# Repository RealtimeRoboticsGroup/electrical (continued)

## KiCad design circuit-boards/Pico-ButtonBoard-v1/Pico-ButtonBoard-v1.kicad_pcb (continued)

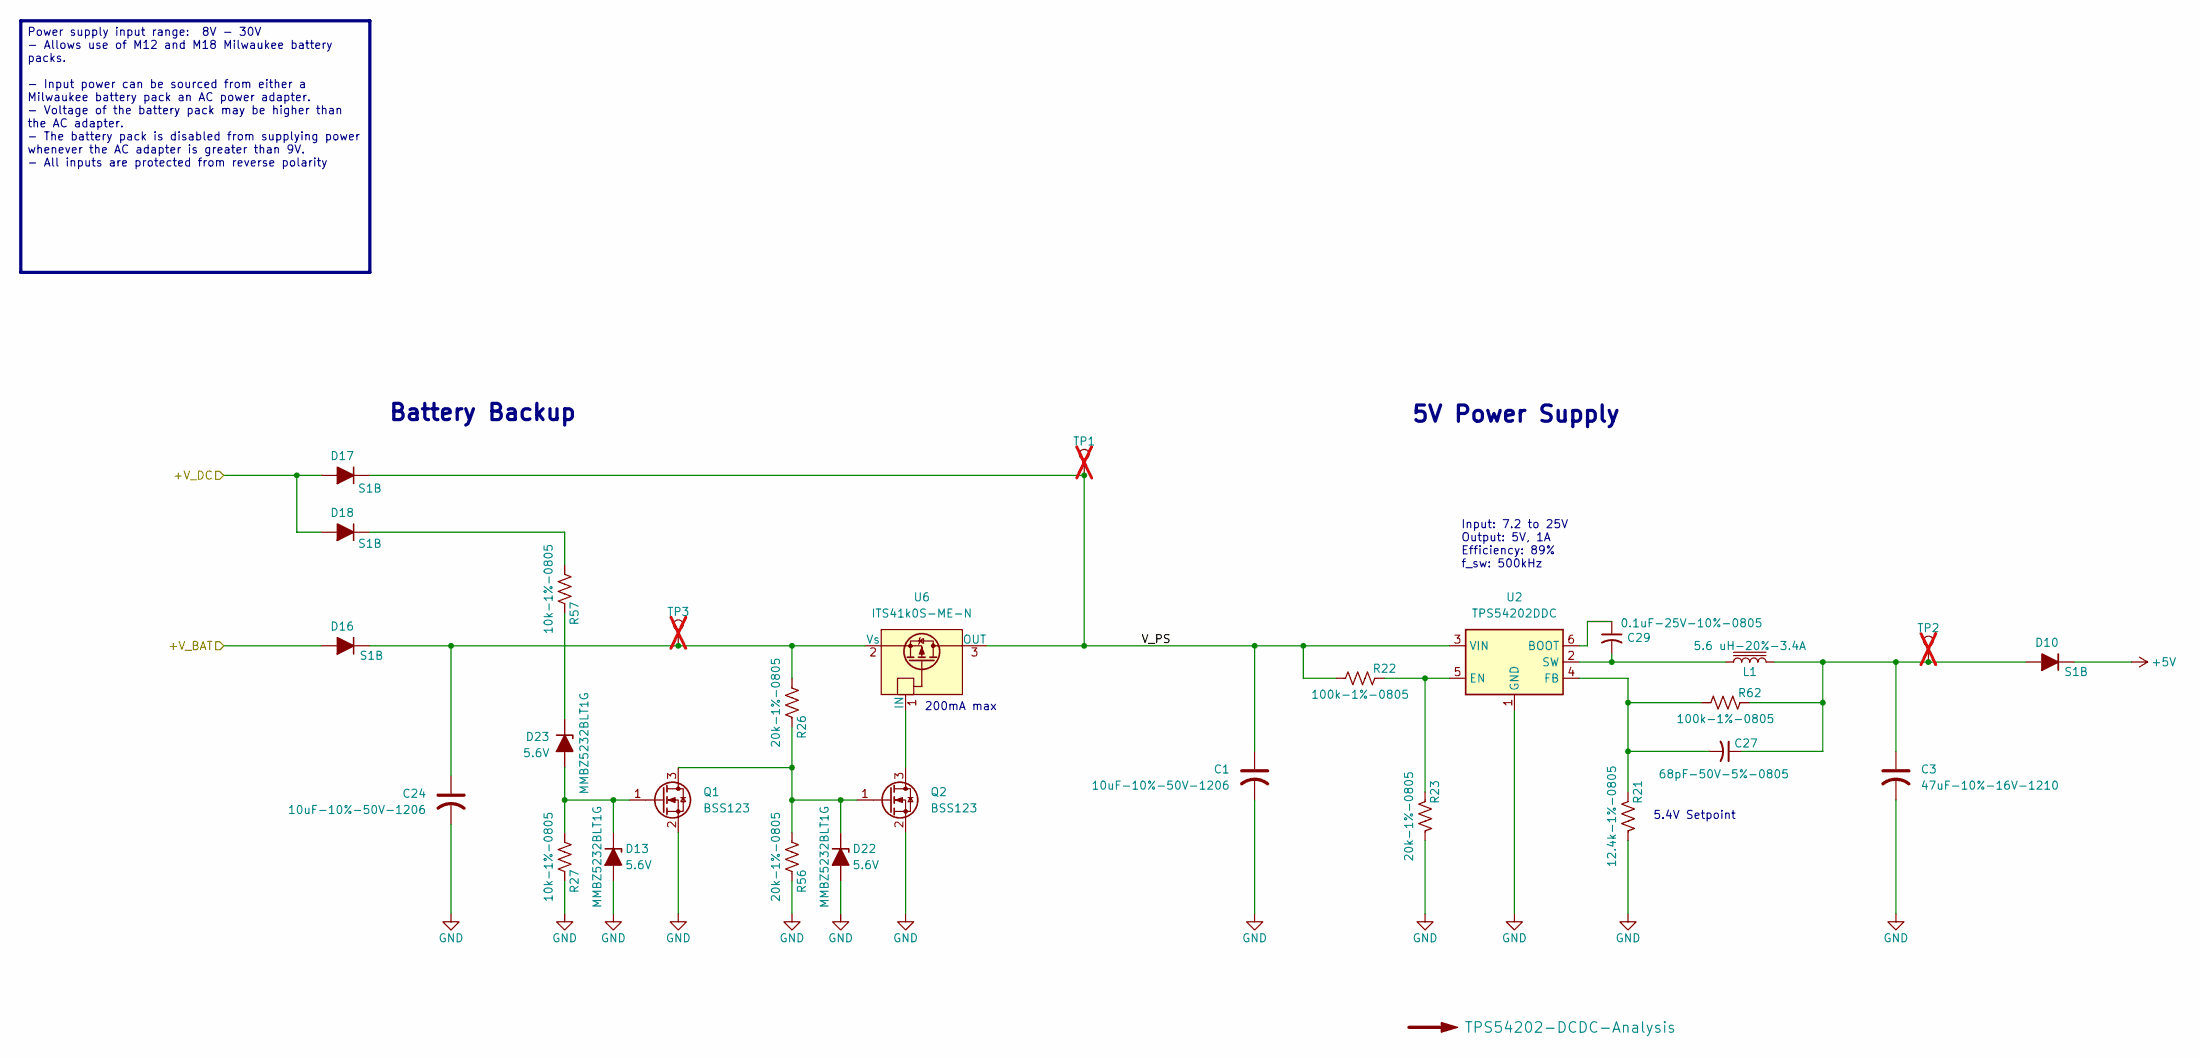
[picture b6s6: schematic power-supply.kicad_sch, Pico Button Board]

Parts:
C1, C24: 10uF-10%-50V-1206; C_1206_3216Metric_Pad1.33x1.80mm_HandSolder; MFG P/N CL31A106KBHNNNE
C3: 47uF-10%-16V-1210; C_1210_3225Metric_Pad1.33x2.70mm_HandSolder; MFG P/N CL32A476KOJNNNE
C27: 68pF-50V-5%-0805; C_0805_2012Metric_Pad1.18x1.45mm_HandSolder; MFG P/N CC0805JRNPO9BN680
C29: 0.1uF-25V-10%-0805; C_0805_2012Metric_Pad1.18x1.45mm_HandSolder; MFG P/N 311-1141-1-ND
D10, D16, D17, D18: S1B; D_SMA; MFG P/N S1B
D13, D22, D23: 5.6V; SOT-23-3; MFG P/N MMBZ5232BLT1G
L1: 5.6 uH-20%-3.4A; Cyntec-MS6-Inductor; MFG P/N VCHA042A-5R6MS6
Q1, Q2: BSS123; SOT-23-3; MFG P/N BSS123
R21: 12.4k-1%-0805; R_0805_2012Metric_Pad1.20x1.40mm_HandSolder; MFG P/N RMCF0805FT12K4
R22, R62: 100k-1%-0805; R_0805_2012Metric_Pad1.20x1.40mm_HandSolder; MFG P/N RC0805FR-07100KL
R23, R26, R56: 20k-1%-0805; R_0805_2012Metric_Pad1.20x1.40mm_HandSolder; MFG P/N ERJ-6ENF2002V
R27, R57: 10k-1%-0805; R_0805_2012Metric_Pad1.20x1.40mm_HandSolder; MFG P/N CRCW080510K0FKEA
TP1, TP2, TP3: CAN_RX; TestPoint_Keystone_5000-5004_Miniature; not fitted
U2: TPS54202DDC; SOT-23-6; MFG P/N TPS54202DDCT
U6: ITS41k0S-ME-N; SOT-223-3_TabPin2; MFG P/N ITS41K0SMENHUMA1

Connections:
+5V: D10.1 (K); also elsewhere on the board
/Power Supply/+V_BAT: D16.2 (A); also elsewhere on the board
/Power Supply/+V_DC: D17.2 (A), D18.2 (A); also elsewhere on the board
/Power Supply/V_PS: C1.1, D17.1 (K), R22.2, TP1.1, U2.3 (VIN), U6.3 (OUT)
GND: C1.2, C3.2, C24.2, D13.1 (A), D22.1 (A), Q1.2 (S), Q2.2 (S), R21.2, R23.2, R27.1, R56.1, U2.1 (GND); also elsewhere on the board
unnamed: C3.1, C27.1, D10.2 (A), L1.2, R62.1, TP2.1
unnamed: D13.3 (K), D23.1 (A), Q1.1 (G), R27.2
unnamed: C24.1, D16.1 (K), R26.2, TP3.1, U6.2 (Vs)
unnamed: D18.1 (K), R57.2
unnamed: D22.3 (K), Q1.3 (D), Q2.1 (G), R26.1, R56.2
unnamed: D23.3 (K), R57.1
unnamed: Q2.3 (D), U6.1 (IN)
unnamed: C29.1, U2.6 (BOOT)
unnamed: R22.1, R23.1, U2.5 (EN)
unnamed: C27.2, R21.1, R62.2, U2.4 (FB)
unnamed: C29.2, L1.1, U2.2 (SW)

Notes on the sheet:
Input: 7.2 to 25V Output: 5V, 1A Efficiency: 89% f_sw: 500kHz
Battery Backup
5V Power Supply
200mA max
5.4V Setpoint
Power supply input range: 8V - 30V - Allows use of M12 and M18 Milwaukee battery packs. - Input power can be sourced from either a Milwaukee battery pack an AC power adapter. - Voltage of the battery pack may be higher than the AC adapter. - The battery pack is disabled from supplying power wheneve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

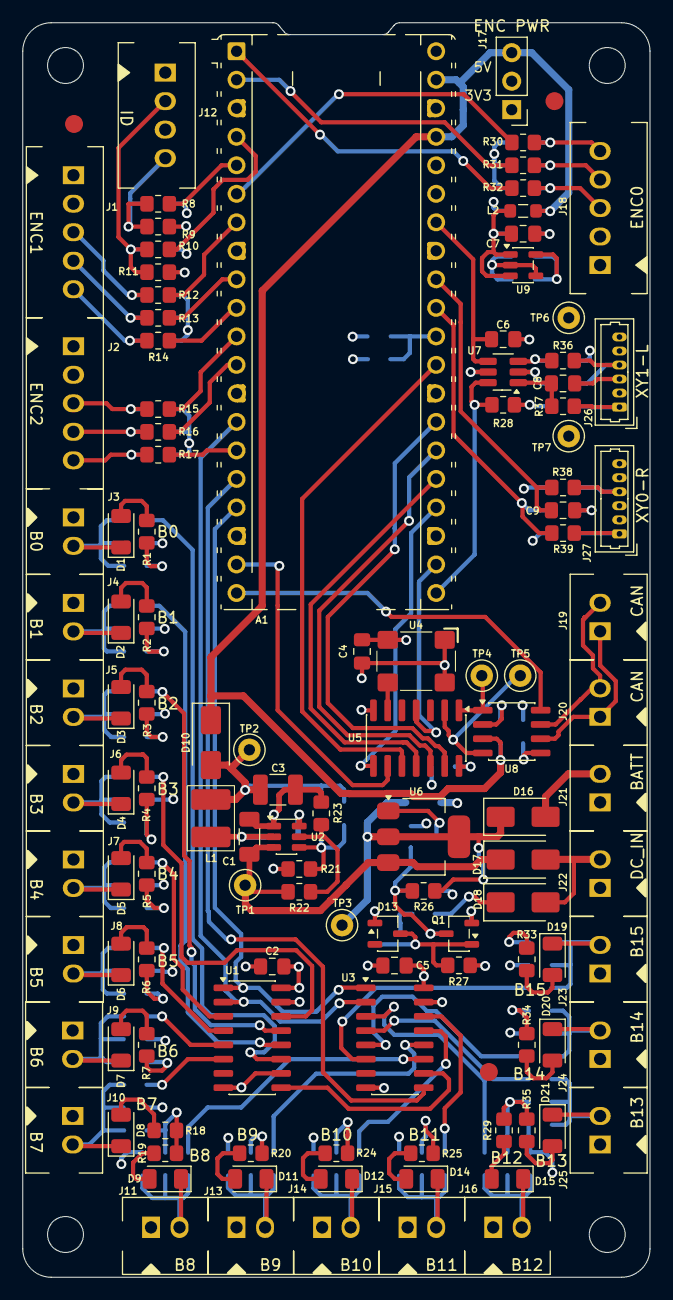
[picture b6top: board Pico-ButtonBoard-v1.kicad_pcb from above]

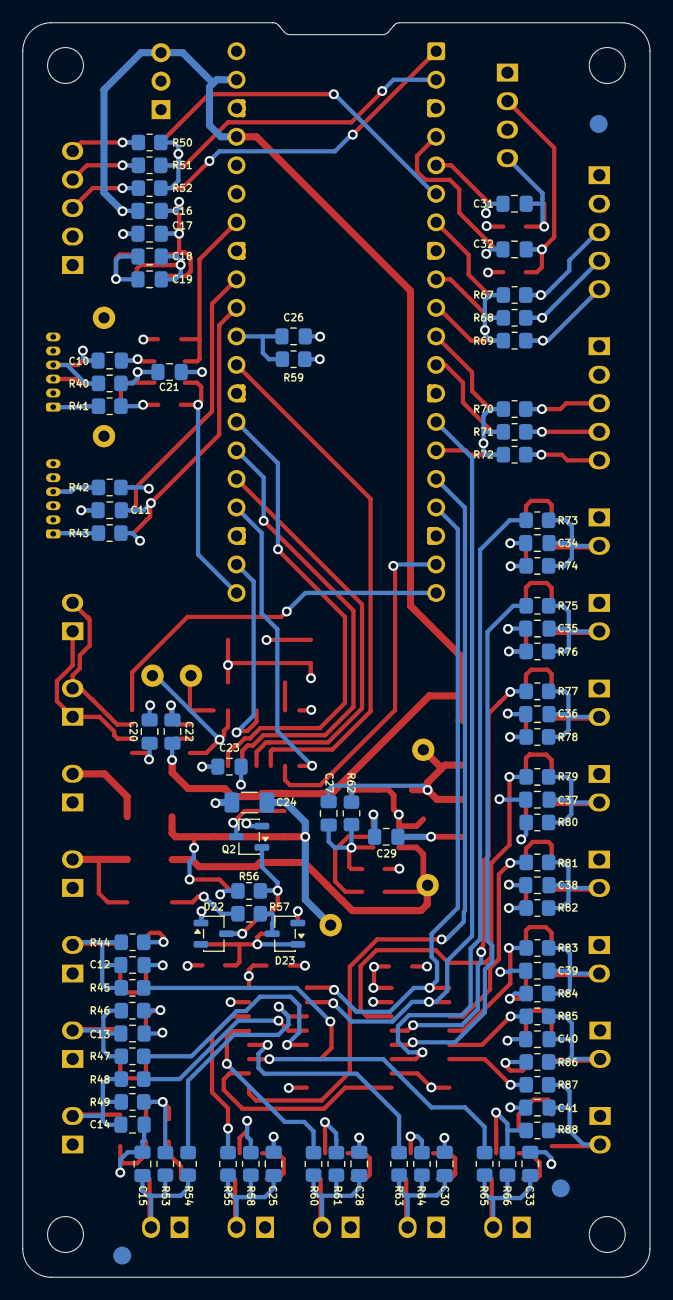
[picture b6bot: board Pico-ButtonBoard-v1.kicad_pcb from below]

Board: 4 copper layers, 55.9 x 111.8 mm, 210 parts (87 on the bottom side), 119 nets.

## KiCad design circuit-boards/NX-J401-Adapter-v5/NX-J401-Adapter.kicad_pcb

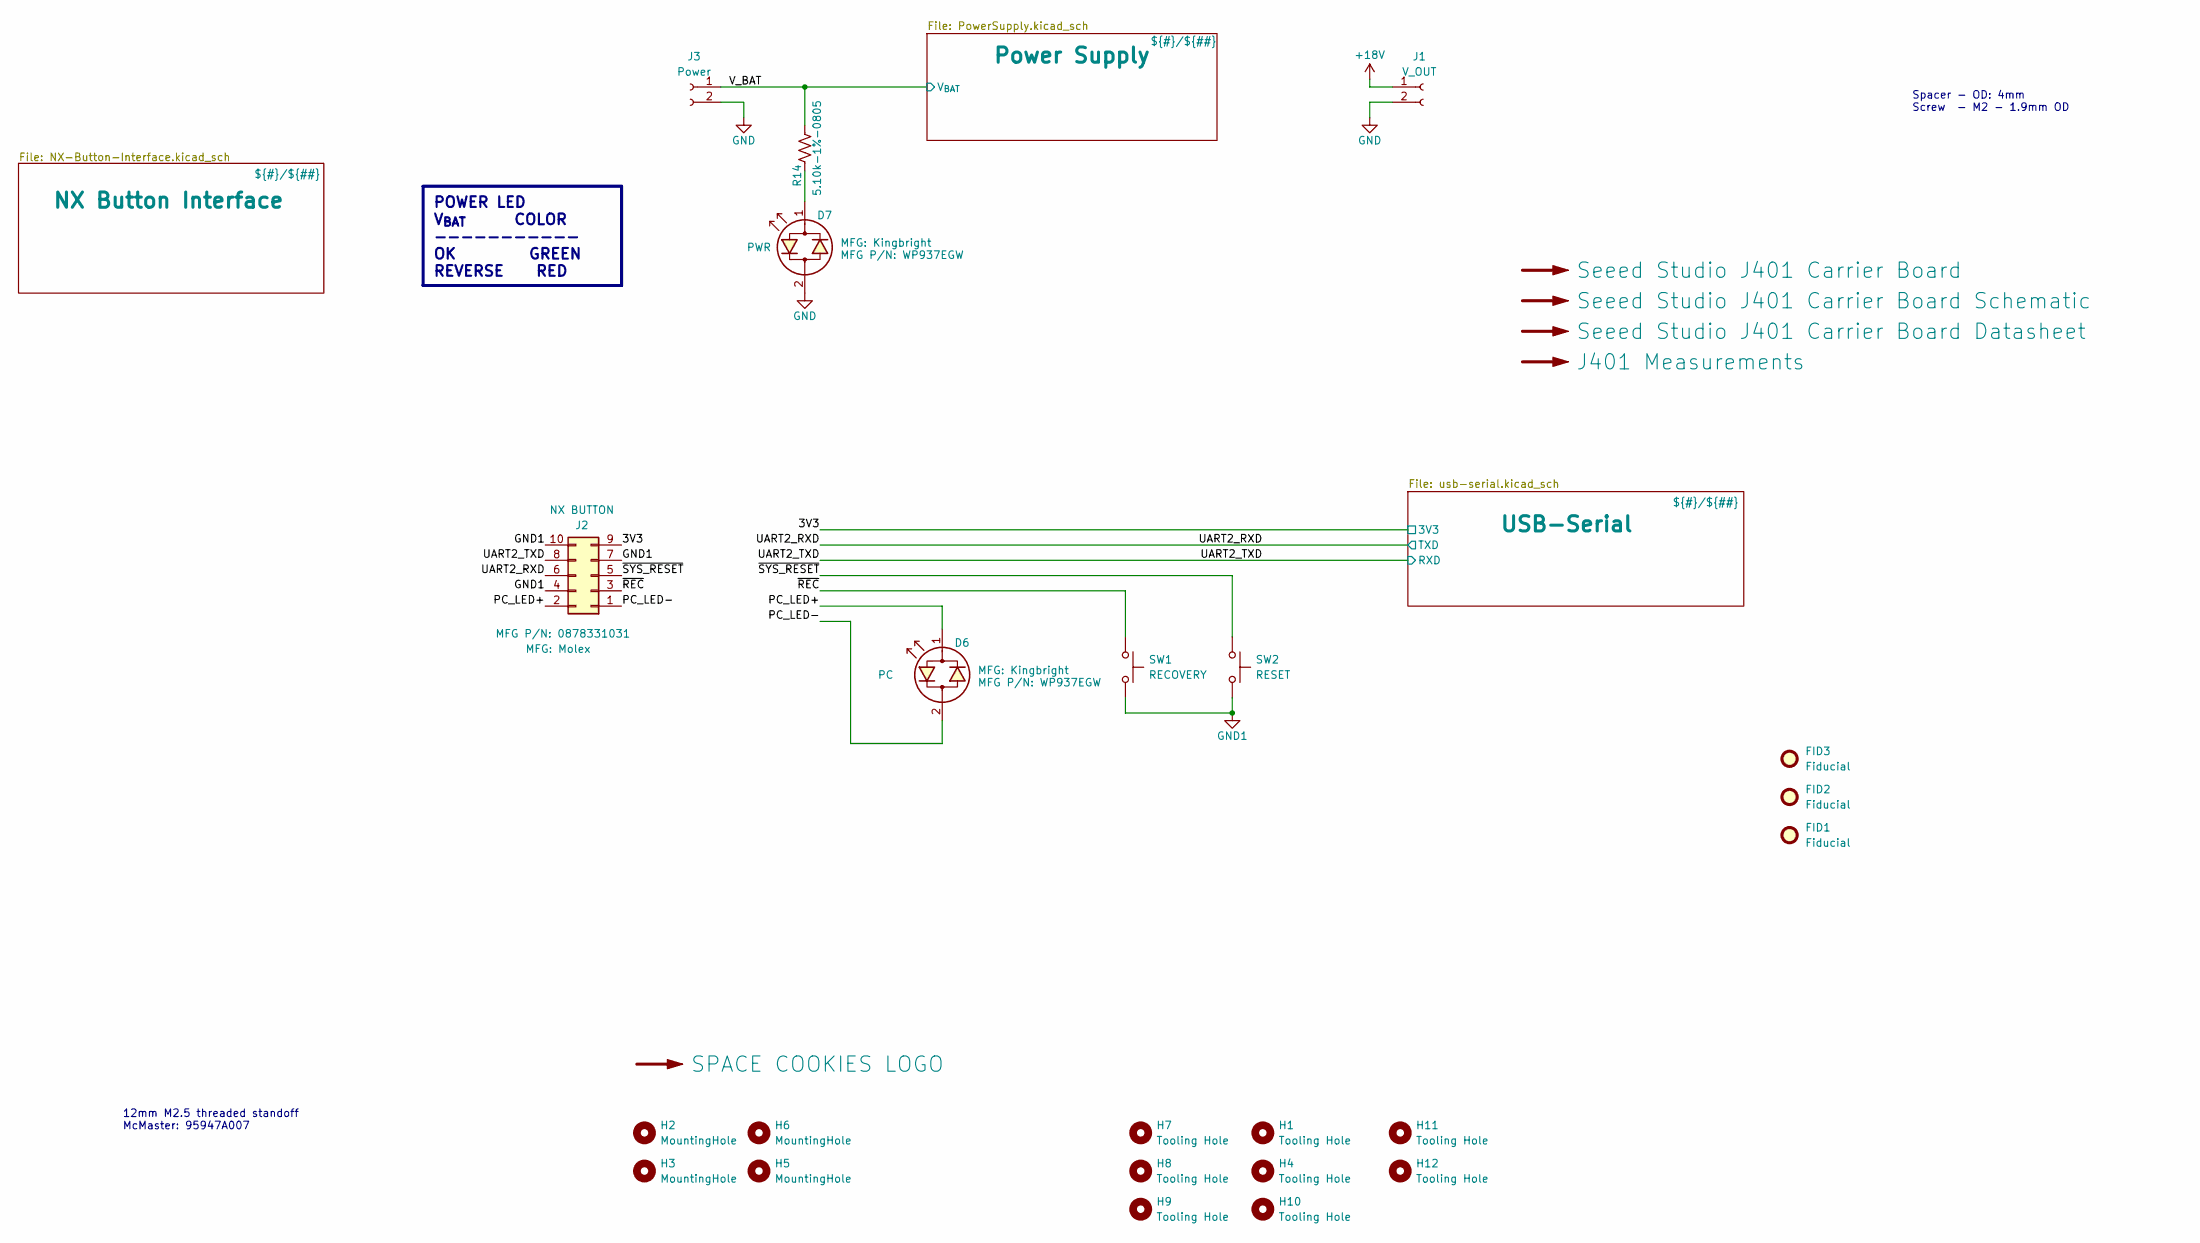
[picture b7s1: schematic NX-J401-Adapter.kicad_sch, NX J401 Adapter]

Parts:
D6: PC; LED_D3.0mm_Horizontal_O1.27mm_Z2.0mm; MFG P/N WP937EGW
D7: PWR; LED_D3.0mm_Horizontal_O1.27mm_Z2.0mm; MFG P/N WP937EGW
FID1, FID2, FID3: Fiducial; Fiducial_1.6mm_Mask3mm
H1, H4, H7, H8, H9, H10, H11, H12: Tooling Hole; ToolingHole_1.152mm
H2, H3, H5, H6: MountingHole; MountingHole_2.7mm_M2.5
J1: V_OUT; Weidmuller-1824740000; MFG P/N 1824740000
J2: NX BUTTON; Molex-0878331031; MFG P/N 0878331031
J3: Power; Weidmuller-1824740000; MFG P/N 1824740000
LOGO1: SPACE COOKIES LOGO; SPACE_COOKIES_LOGO_15mm
R14: 5.10k-1%-0805; R_0805_2012Metric; MFG P/N RC0805FR-075K1L
SW1: RECOVERY; SW_TL1105VF100Q_EWI; MFG P/N TL1105VF100Q
SW2: RESET; SW_TL1105VF100Q_EWI; MFG P/N TL1105VF100Q

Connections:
+18V: J1.1; also elsewhere on the board
/3V3: J2.9; also elsewhere on the board
/PC_LED+: D6.1 (KA), J2.2
/PC_LED-: D6.2 (AK), J2.1
/UART2_RXD: J2.6; also elsewhere on the board
/UART2_TXD: J2.8; also elsewhere on the board
/V_BAT: J3.1, R14.1; also elsewhere on the board
/~REC: J2.3, SW1.1
/~SYS_RESET: J2.5, SW2.1
GND: D7.2 (AK), J1.2, J3.2; also elsewhere on the board
GND1: J2.4, J2.7, J2.10, SW1.2, SW2.2; also elsewhere on the board
unnamed: D7.1 (KA), R14.2

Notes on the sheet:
12mm M2.5 threaded standoff McMaster: 95947A007
Spacer - OD: 4mm Screw - M2 - 1.9mm OD
POWER LED V_{BAT} COLOR ----------- OK GREEN REVERSE RED

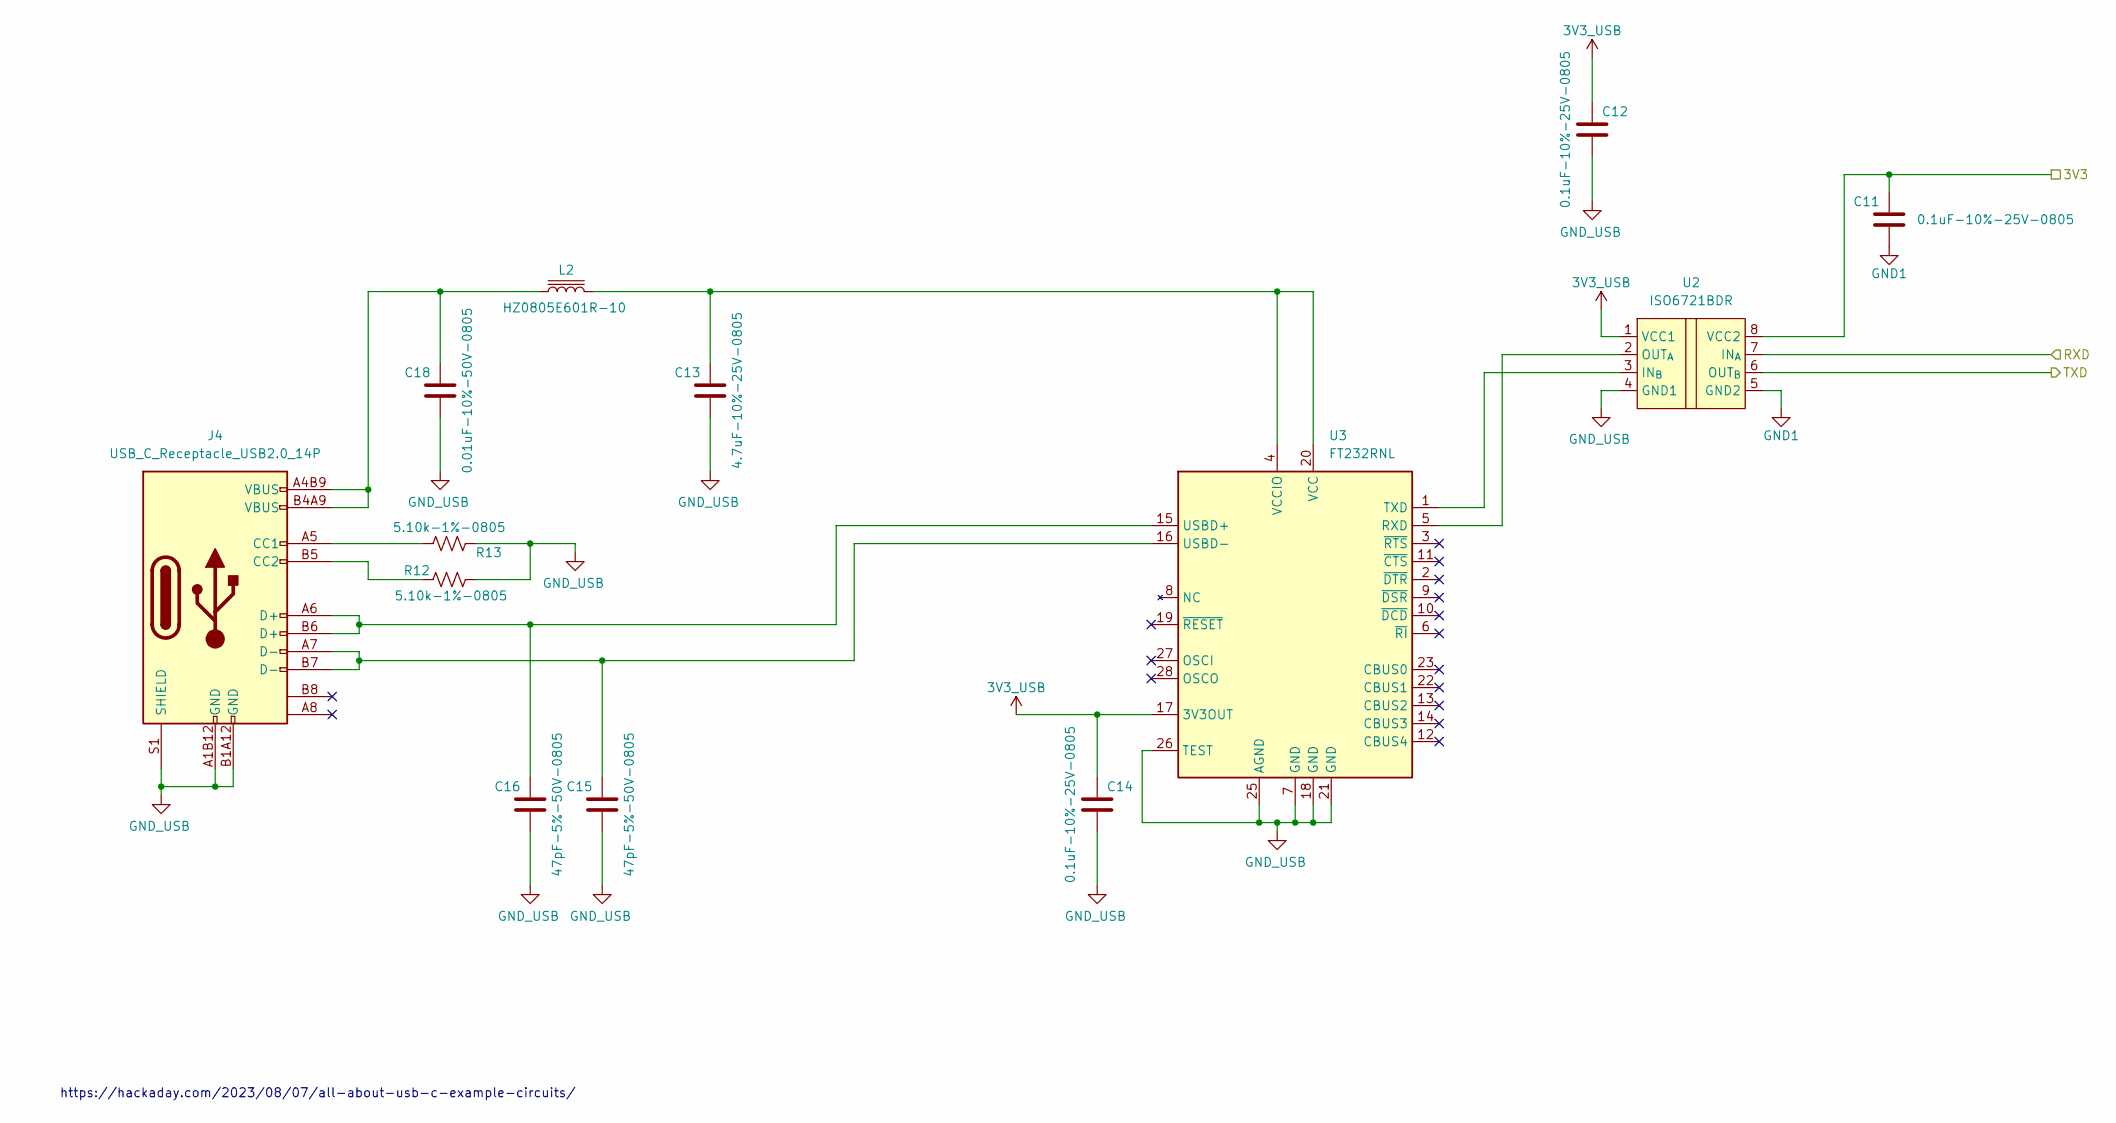
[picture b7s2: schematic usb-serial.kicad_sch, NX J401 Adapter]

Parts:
C11, C12, C14: 0.1uF-10%-25V-0805; C_0805_2012Metric; MFG P/N C0805C104K3RACTU
C13: 4.7uF-10%-25V-0805; C_0805_2012Metric; MFG P/N CL21A475KAQNNNE
C15, C16: 47pF-5%-50V-0805; C_0805_2012Metric; MFG P/N CC0805JRNPO9BN470
C18: 0.01uF-10%-50V-0805; C_0805_2012Metric; MFG P/N CL21B103KBANNNC
J4: USB_C_Receptacle_USB2.0_14P; Molex-USB-C-2171790001; MFG P/N 2171790001
L2: HZ0805E601R-10; L_0805_2012Metric; MFG P/N HZ0805E601R-10
R12, R13: 5.10k-1%-0805; R_0805_2012Metric; MFG P/N RC0805FR-075K1L
U2: ISO6721BDR; SOIC-8_3.9x4.9mm_P1.27mm; MFG P/N ISO6721BDR
U3: FT232RNL; SSOP-28_5.3x10.2mm_P0.65mm; MFG P/N FT232RNL

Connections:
3V3_USB: C12.1, C14.1, U2.1 (VCC1), U3.17 (3V3OUT)
/3V3: C11.1, U2.8 (VCC2); also elsewhere on the board
/UART2_RXD: U2.6 (OUT_{B}); also elsewhere on the board
/UART2_TXD: U2.7 (IN_{A}); also elsewhere on the board
GND1: C11.2, U2.5 (GND2); also elsewhere on the board
GND_USB: C12.2, C13.2, C14.2, C15.2, C16.2, C18.2, J4.A1B12 (GND), J4.B1A12 (GND), J4.S1 (SHIELD), R12.1, R13.1, U2.4 (GND1), U3.7 (GND), U3.18 (GND), U3.21 (GND), U3.25 (AGND), U3.26 (TEST)
unnamed: C18.1, J4.A4B9 (VBUS), J4.B4A9 (VBUS), L2.1
unnamed: J4.A5 (CC1), R13.2
unnamed: J4.B5 (CC2), R12.2
unnamed: U2.3 (IN_{B}), U3.1 (TXD)
unnamed: U2.2 (OUT_{A}), U3.5 (RXD)
unnamed: C16.1, J4.A6 (D+), J4.B6 (D+), U3.15 (USBD+)
unnamed: C15.1, J4.A7 (D-), J4.B7 (D-), U3.16 (USBD-)
unnamed: C13.1, L2.2, U3.4 (VCCIO), U3.20 (VCC)

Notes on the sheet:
https://hackaday.com/2023/08/07/all-about-usb-c-example-circuits/

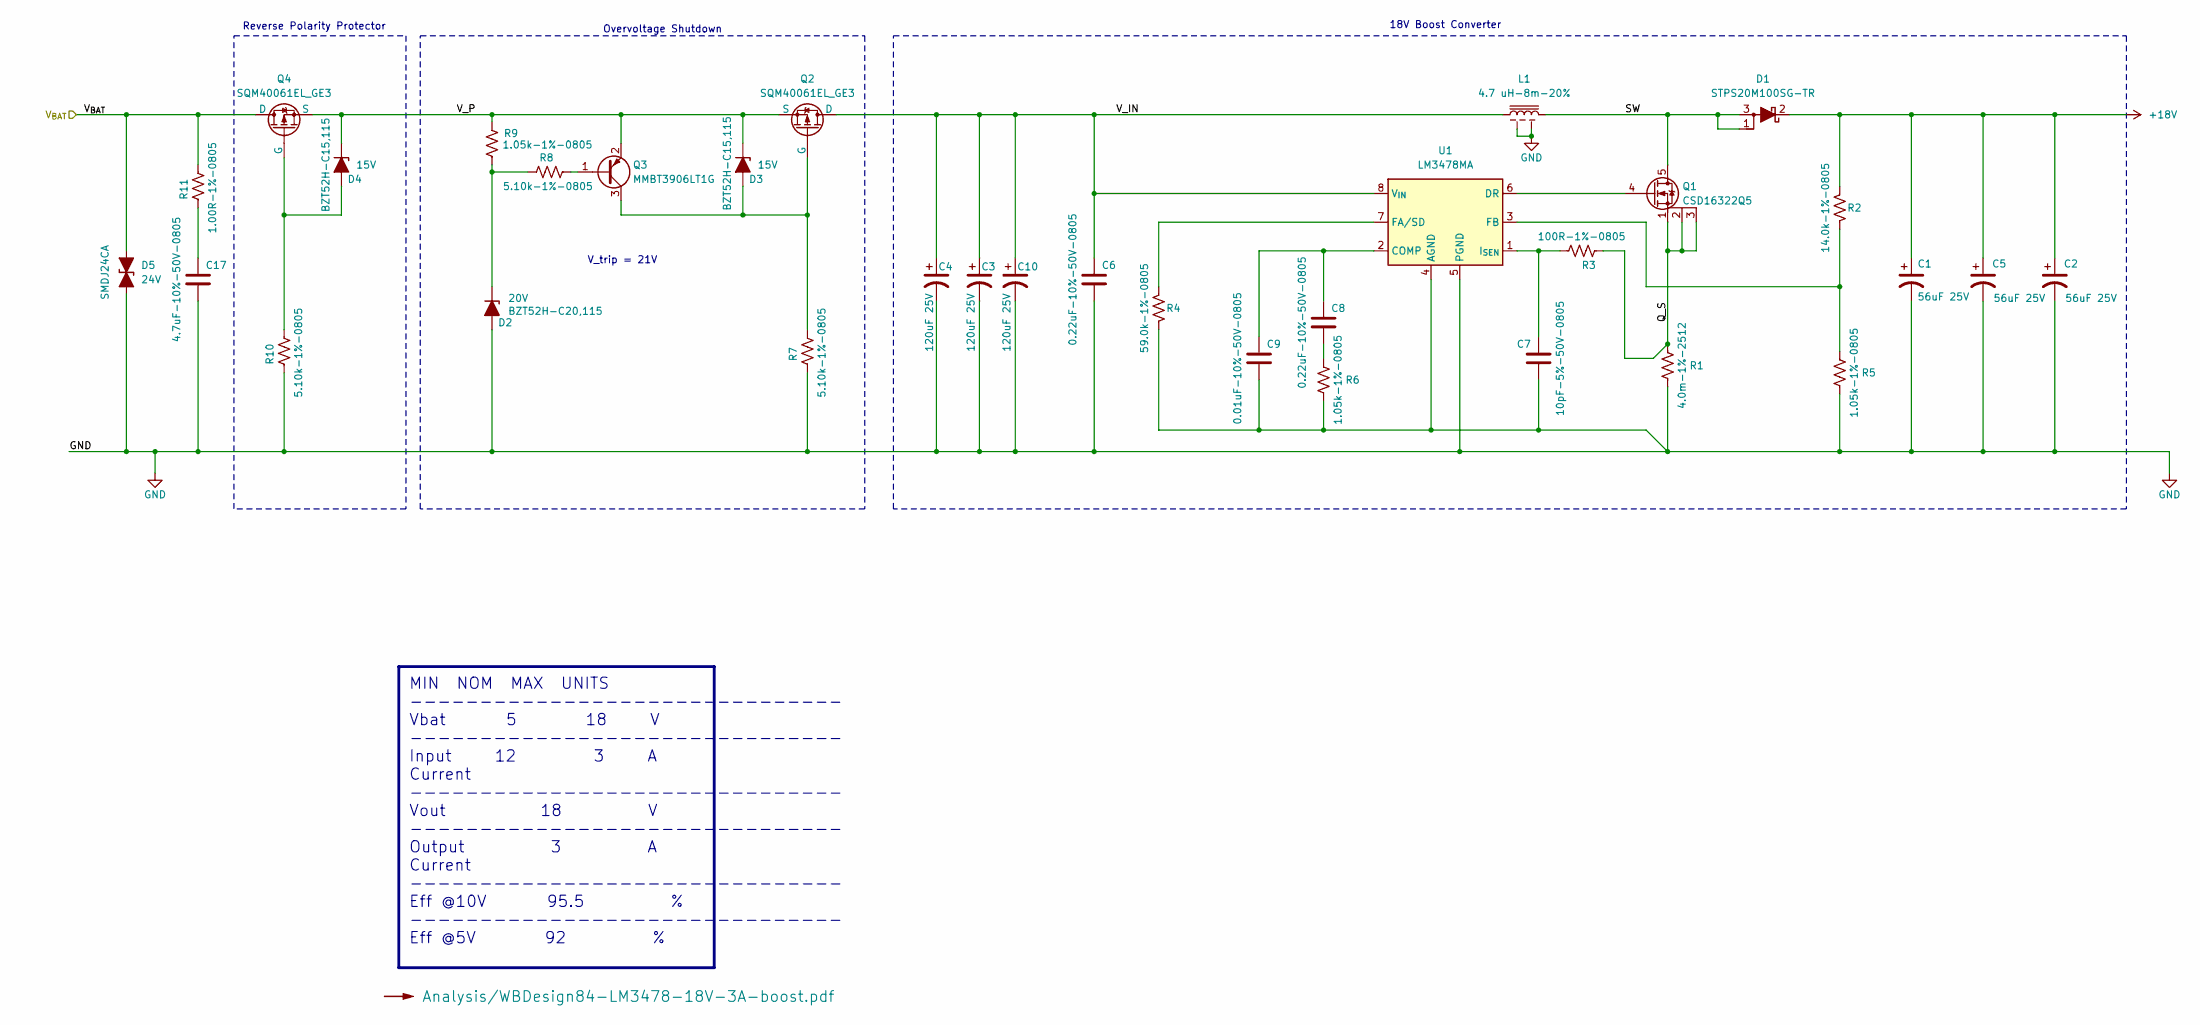
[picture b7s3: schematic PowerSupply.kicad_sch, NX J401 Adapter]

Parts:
C1, C2, C5: 56uF 25V; CP_Radial_D8.0mm_P3.50mm_H7.0mm; MFG P/N 25SEPF56M
C3, C4, C10: 120uF 25V; CP_Radial_D8.0mm_P3.50mm_H7.0mm; MFG P/N 25SEK120M
C6, C8: 0.22uF-10%-50V-0805; C_0805_2012Metric; MFG P/N C0805C224K5RAC7800
C7: 10pF-5%-50V-0805; C_0805_2012Metric; MFG P/N CL21C100CBANNNC
C9: 0.01uF-10%-50V-0805; C_0805_2012Metric; MFG P/N CL21B103KBANNNC
C17: 4.7uF-10%-50V-0805; C_0805_2012Metric; MFG P/N GRM21BR61H475KE51L
D1: STPS20M100SG-TR; TO-263-2; MFG P/N STPS20M100SG-TR
D2: 20V; D_SOD-123F; MFG P/N BZT52H-C20,115
D3, D4: 15V; D_SOD-123F; MFG P/N BZT52H-C15,115
D5: 24V; D_SMC_Littelfuse_DO-214AB; MFG P/N SMDJ24CA
L1: 4.7 uH-8m-20%; INDUCTOR_IHLE-5050FH-Vishay; MFG P/N IHLE5050FHER4R7M5A
Q1: CSD16322Q5; TI-SON5x6; MFG P/N CSD16322Q5
Q2, Q4: SQM40061EL_GE3; TO-263-2; MFG P/N SQM40061EL_GE3
Q3: MMBT3906LT1G; SOT-23; MFG P/N MMBT3906LT1G
R1: 4.0m-1%-2512; R_2512_6332Metric; MFG P/N CRE2512-FZ-R004E-3
R2: 14.0k-1%-0805; R_0805_2012Metric; MFG P/N RC0805FR-0714KL
R3: 100R-1%-0805; R_0805_2012Metric; MFG P/N RC0805FR-07100RL
R4: 59.0k-1%-0805; R_0805_2012Metric; MFG P/N RC0805FR-0759KL
R5, R6, R9: 1.05k-1%-0805; R_0805_2012Metric; MFG P/N RC0805FR-071K05L
R7, R8, R10: 5.10k-1%-0805; R_0805_2012Metric; MFG P/N RC0805FR-075K1L
R11: 1.00R-1%-0805; R_0805_2012Metric; MFG P/N CRCW08051R00FKEAHP
U1: LM3478MA; SOIC-8_3.9x4.9mm_P1.27mm; MFG P/N LM3478MAX/NOPB

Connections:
+18V: C1.1, C2.1, C5.1, D1.2 (K), R2.2; also elsewhere on the board
/Power Supply/Q_S: Q1.1 (S), Q1.2 (S), Q1.3 (S), R1.2, R3.1
/Power Supply/SW: D1.1 (A), D1.3 (A), L1.2, Q1.5 (D)
/Power Supply/V_IN: C3.1, C4.1, C6.1, C10.1, L1.1, Q2.2 (D), U1.8 (V_{IN})
/Power Supply/V_P: D3.1 (K), D4.1 (K), Q2.3 (S), Q3.2 (E), Q4.3 (S), R9.2
/V_BAT: D5.2 (A2), Q4.2 (D), R11.2; also elsewhere on the board
GND: C1.2, C2.2, C3.2, C4.2, C5.2, C6.2, C7.2, C9.2, C10.2, C17.2, D2.2 (A), D5.1 (A1), L1.3, L1.4, R1.1, R4.1, R5.1, R6.1, R7.1, R10.1, U1.4 (AGND), U1.5 (PGND); also elsewhere on the board
unnamed: C8.2, R6.2
unnamed: C17.1, R11.1
unnamed: D2.1 (K), R8.1, R9.1
unnamed: D3.2 (A), Q2.1 (G), Q3.3 (C), R7.2
unnamed: D4.2 (A), Q4.1 (G), R10.2
unnamed: Q1.4 (G), U1.6 (DR)
unnamed: Q3.1 (B), R8.2
unnamed: C8.1, C9.1, U1.2 (COMP)
unnamed: R4.2, U1.7 (FA/SD)
unnamed: R2.1, R5.2, U1.3 (FB)
unnamed: C7.1, R3.2, U1.1 (I_{SEN})

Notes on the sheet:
Reverse Polarity Protector
V_trip = 21V
18V Boost Converter
Overvoltage Shutdown
MIN NOM MAX UNITS ------------------------------- Vbat 5 18 V ------------------------------- Input 12 3 A Current ------------------------------- Vout 18 V ------------------------------- Output 3 A Current ------------------------------- Eff @10V 95.5 % ------------------------------- Eff @5V 92 %

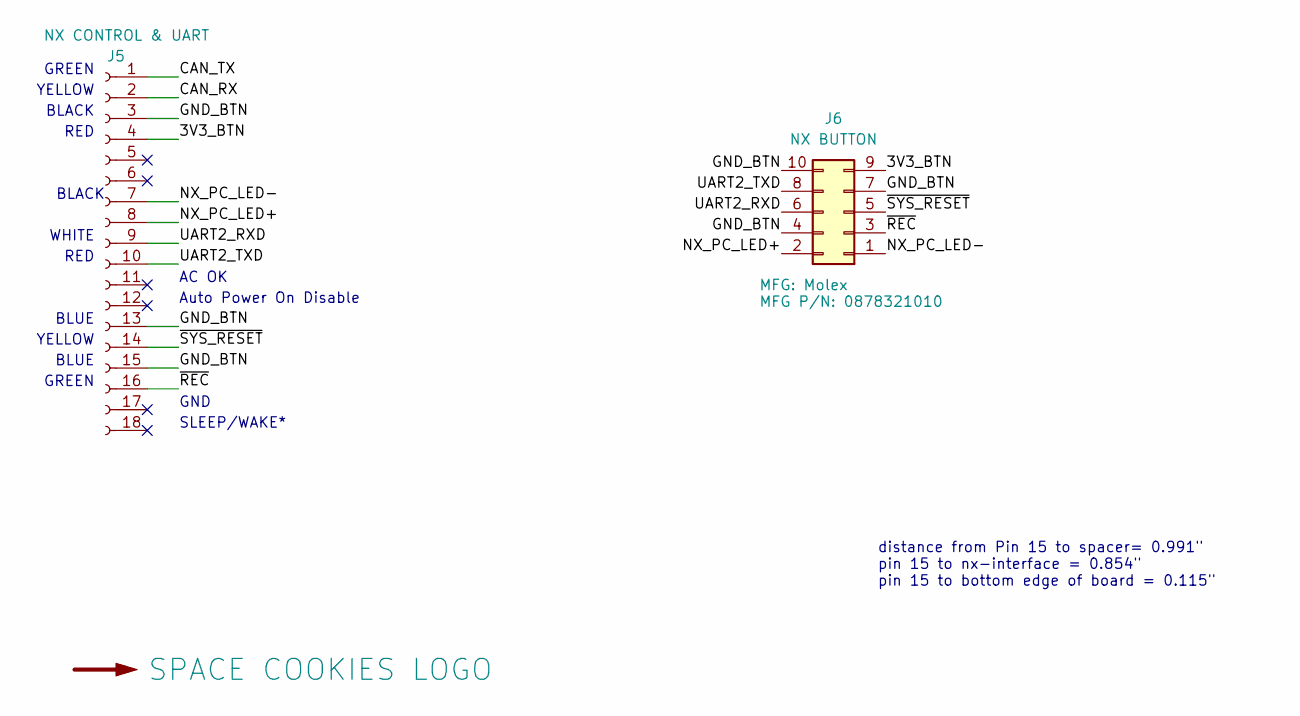
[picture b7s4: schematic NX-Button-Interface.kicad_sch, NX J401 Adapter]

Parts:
J5: NX CONTROL & UART; PinSocket_1x18_P2.54mm_Vertical; MFG P/N PPTC181LFBN-RC
J6: NX BUTTON; Molex-878321010; MFG P/N 0878321010
LOGO2: SPACE COOKIES LOGO; SPACE_COOKIES_LOGO_15mm

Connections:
/NX Button Interface/3V3_BTN: J5.4, J6.9
/NX Button Interface/CAN_RX: J5.2
/NX Button Interface/CAN_TX: J5.1
/NX Button Interface/GND_BTN: J5.3, J5.13, J5.15, J6.4, J6.7, J6.10
/NX Button Interface/NX_PC_LED+: J5.8, J6.2
/NX Button Interface/NX_PC_LED-: J5.7, J6.1
/NX Button Interface/UART2_RXD: J5.9, J6.6
/NX Button Interface/UART2_TXD: J5.10, J6.8
/NX Button Interface/~REC: J5.16, J6.3
/NX Button Interface/~SYS_RESET: J5.14, J6.5

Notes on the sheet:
BLACK
YELLOW
BLUE
RED
AC OK
GND
Auto Power On Disable
SLEEP/WAKE*
GREEN
distance from Pin 15 to spacer= 0.991" pin 15 to nx-interface = 0.854" pin 15 to bottom edge of board = 0.115"
WHITE

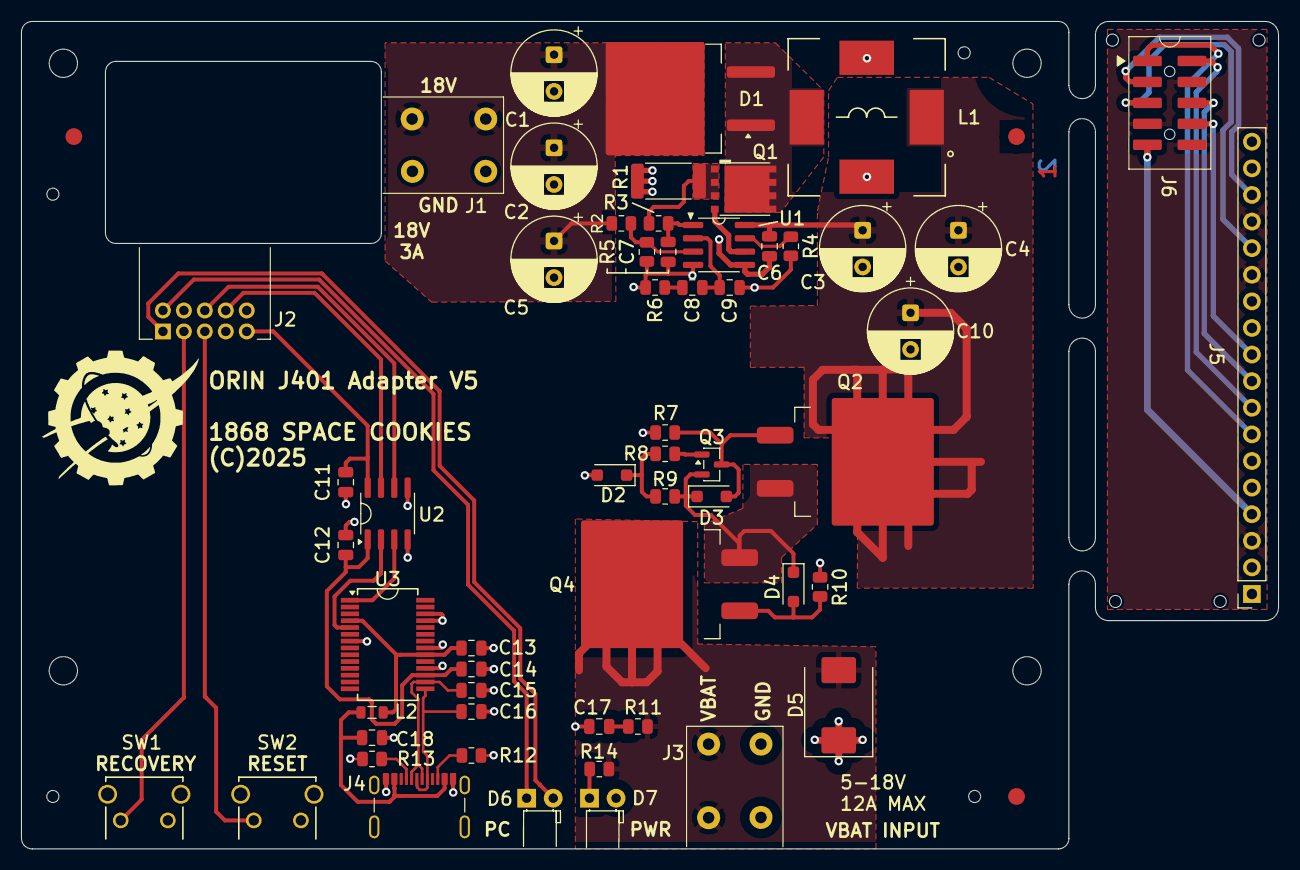
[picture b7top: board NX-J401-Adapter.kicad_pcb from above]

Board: 2 copper layers, 120.0 x 79.0 mm, 73 parts (1 on the bottom side), 45 nets.

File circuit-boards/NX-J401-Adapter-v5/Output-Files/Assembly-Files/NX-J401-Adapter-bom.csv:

"Item","QUANTITY","Reference","Value","MFG","MFG P/N","DIST","DIST P/N"
"1","1","C7","10pF-5%-50V-0805","Samsung Electro-Mechanics","CL21C100CBANNNC","Digikey","1276-2561-1-ND"
"2","1","C13","4.7uF-10%-25V-0805","Samsung Electro-Mechanics","CL21A475KAQNNNE","Digikey","1276-1244-1-ND"
"3","1","C17","4.7uF-10%-50V-0805","Murata Electronics","GRM21BR61H475KE51L","Digikey","490-10751-1-ND"
"4","3","C1,C2,C5","56uF 25V","Panasonic Electronic Components","25SEPF56M","Mouser","667-25SEPF56M "
"5","3","C11,C12,C14","0.1uF-10%-25V-0805","KEMET","C0805C104K3RACTU","Digikey","399-C0805C104K3RACTUCT-ND"
"6","2","C15,C16","47pF-5%-50V-0805","YAGEO","CC0805JRNPO9BN470","Digikey","311-1107-1-ND"
"7","3","C3,C4,C10","120uF 25V","Panasonic","25SEK120M","Digikey","P122635-ND"
"8","2","C6,C8","0.22uF-10%-50V-0805","KEMET","C0805C224K5RAC7800","Digikey","399-C0805C224K5RACTUCT-ND"
"9","2","C9,C18","0.01uF-10%-50V-0805","Samsung Electro-Mechanics","CL21B103KBANNNC","Digikey","1276-1015-1-ND"
"10","1","D1","STPS20M100SG-TR","STmicroelectronics","STPS20M100SG-TR","Digikey","497-10993-1-ND"
"11","1","D2","20V","Nexperia","BZT52H-C20,115","Digikey","1727-3596-1-ND"
"12","1","D5","24V","Littelfuse","SMDJ24CA","Digikey","SMDJ24CACT-ND"
"13","2","D3,D4","15V","Nexperia","BZT52H-C15,115","Digikey","1727-3593-1-ND"
"14","2","D6,D7","PC,PWR","Kingbright","WP937EGW","Digikey","754-1751-ND"
"15","1","J2","NX BUTTON","Molex","0878321010","Digikey","WM4227-ND"
"16","1","J4","USB_C_Receptacle_USB2.0_14P","Molex","2171790001","Digikey","900-2171790001CT-ND"
"17","2","J1,J3","Power,V_OUT","Weidmuller","1824740000","Digikey","281-2110-ND"
"18","1","L1","4.7 uH-8m-20%","Vishay Dale","IHLE5050FHER4R7M5A ","Mouser","70-IHLE5050FHR4R7M5A "
"19","1","L2","HZ0805E601R-10","Laird-Signal Integrity Products","HZ0805E601R-10","Digikey","240-2399-1-ND"
"20","1","Q1","CSD16322Q5","Texas Instruments","CSD16322Q5","Digikey","296-25112-1-ND"
"21","1","Q3","MMBT3906LT1G","onsemi","MMBT3906LT1G","Digikey","MMBT3906LT1GOSCT-ND"
"22","2","Q2,Q4","SQM40061EL_GE3","Vishay Siliconix","SQM40061EL_GE3","Digikey","SQM40061EL_GE3CT-ND"
"23","1","R1","4.0m-1%-2512","Bourns Inc.","CRE2512-FZ-R004E-3","Digikey","CRE2512-FZ-R004E-3CT-ND"
"24","1","R2","14.0k-1%-0805","Yageo","RC0805FR-0714KL","Digikey","311-14.0KCRCT-ND"
"25","1","R3","100R-1%-0805","Yageo","RC0805FR-07100RL","Digikey","311-100CRCT-ND"
"26","1","R4","59.0k-1%-0805","Yageo","RC0805FR-0759KL","Digikey","311-59.0KCRCT-ND"
"27","1","R11","1.00R-1%-0805","Vishay Dale","CRCW08051R00FKEAHP","Digikey","541-1.00TCT-ND"
"28","3","R5,R6,R9","1.05k-1%-0805","Yageo","RC0805FR-071K05L","Digikey","311-1.05KCRCT-ND"
"29","6","R7,R8,R10,R12-R14","5.10k-1%-0805","Yageo","RC0805FR-075K1L","Digikey","311-5.10KCRCT-ND"
"30","2","SW1,SW2","RECOVERY,RESET","E-Switch","TL1105VF100Q","Digikey","EG2507-ND"
"31","1","U1","LM3478MA","Texas Instruments","LM3478MAX/NOPB","Digikey","296-38111-1-ND"
"32","1","U2","ISO6721BDR","Texas Instruments","ISO6721BDR","Digikey","296-ISO6721BDRCT-ND"
"33","1","U3","FT232RNL","FTDI","FT232RNL","Digikey","768-FT232RNL-REELCT-ND"

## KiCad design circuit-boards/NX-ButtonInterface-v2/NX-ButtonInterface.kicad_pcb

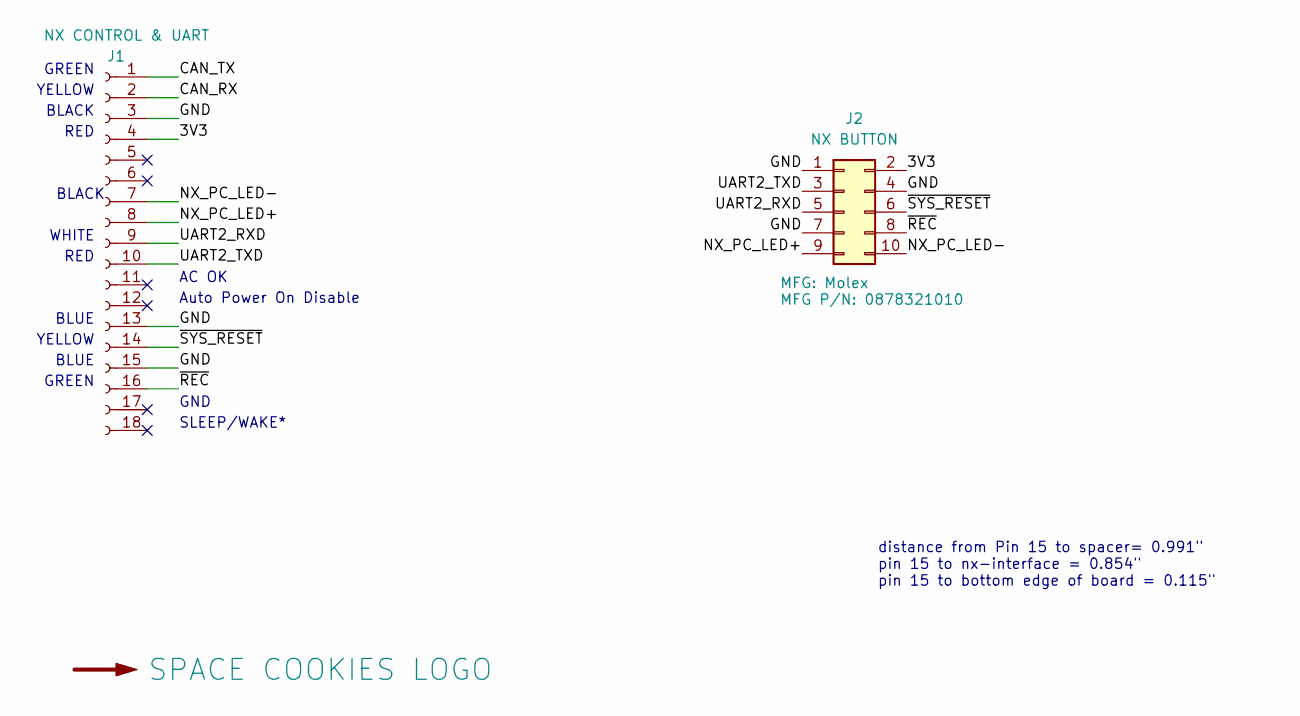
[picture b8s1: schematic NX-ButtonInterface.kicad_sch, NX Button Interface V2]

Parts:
J1: NX CONTROL & UART; PinSocket_1x18_P2.54mm_Vertical; MFG P/N PPTC181LFBN-RC
J2: NX BUTTON; Molex-878321010; MFG P/N 0878321010
LOGO1: SPACE COOKIES LOGO; SPACE_COOKIES_LOGO_15mm

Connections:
/3V3: J1.4, J2.2
/CAN_RX: J1.2
/CAN_TX: J1.1
/GND: J1.3, J1.13, J1.15, J2.1, J2.4, J2.7
/NX_PC_LED+: J1.8, J2.9
/NX_PC_LED-: J1.7, J2.10
/UART2_RXD: J1.9, J2.5
/UART2_TXD: J1.10, J2.3
/~REC: J1.16, J2.8
/~SYS_RESET: J1.14, J2.6

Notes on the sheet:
RED
YELLOW
distance from Pin 15 to spacer= 0.991" pin 15 to nx-interface = 0.854" pin 15 to bottom edge of board = 0.115"
GREEN
BLACK
WHITE
BLUE
AC OK
GND
Auto Power On Disable
SLEEP/WAKE*

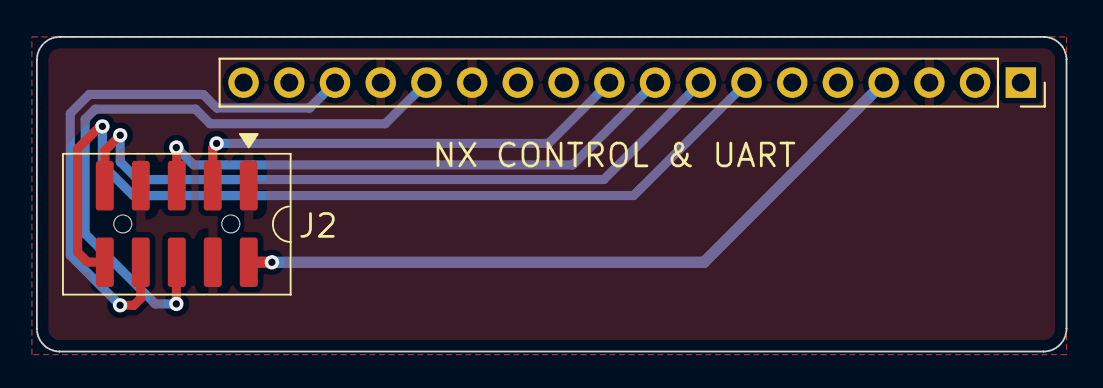
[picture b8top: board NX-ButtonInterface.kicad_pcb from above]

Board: 2 copper layers, 57.2 x 17.5 mm, 3 parts (1 on the bottom side), 8 nets.

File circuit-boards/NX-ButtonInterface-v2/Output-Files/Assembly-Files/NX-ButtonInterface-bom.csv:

"Item","QUANTITY","Reference","Value","MFG","MFG P/N","DIST","DIST P/N"
"1","1","J1","NX CONTROL & UART","Sullins Connector Solutions","PPTC181LFBN-RC","Digikey","S7016-ND"
"2","1","J2","NX BUTTON","Molex","0878321010","Digikey","WM4227-ND"
